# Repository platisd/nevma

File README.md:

# Nevma
A USB gadget to transform your gestures to keyboard and mouse events.

## Overview
Nevma (means "gesture" in Greek) is a simple to build, program and use device that translates your hand gestures into keyboard and mouse input. Just plug it in your USB port and magically wave through your presentations, documents, pictures, songs and the like.

## How does it work
Nevma implements two basic functions. Gesture recognition and keyboard and mouse event generation over USB. The former is realized through the [APDS-9960](https://learn.sparkfun.com/tutorials/apds-9960-rgb-and-gesture-sensor-hookup-guide) sensor while the latter by utilizing the USB HID capabilities of the ATMega32U4 chip.

Nevma can by default recognize a plethora of gestures; swipe left, right, up, down, and moving the hand closer or further from the sensor, using the [APDS-9960 library](https://github.com/sparkfun/SparkFun_APDS-9960_Sensor_Arduino_Library) by Sparkfun.

## Components
* [Nevma board PCB](https://www.pcbway.com/project/shareproject/Nevma__Gesture_control_for_the_masses.html)
* [3D printed case](https://www.tinkercad.com/things/h5ymCb1lX3J)
* [Mini SS Micro ATMEGA32U4](https://www.aliexpress.com/item/New-Arrival-Mini-SS-Micro-ATMEGA32U4-Pro-Micro-Module-Board-Compatible-For-Arduino/32777411276.html)
* [APDS-9960 module](https://www.aliexpress.com/item/GY-9960LLC-APDS-9960-RGB-and-Gesture-Sensor-Module-I2C-Breakout-for-Arduino/32746930049.html)

## Media
*  [Nevma: Gesture control for the masses](https://platis.solutions/blog/2017/11/27/nevma-gesture-control-for-the-masses/)

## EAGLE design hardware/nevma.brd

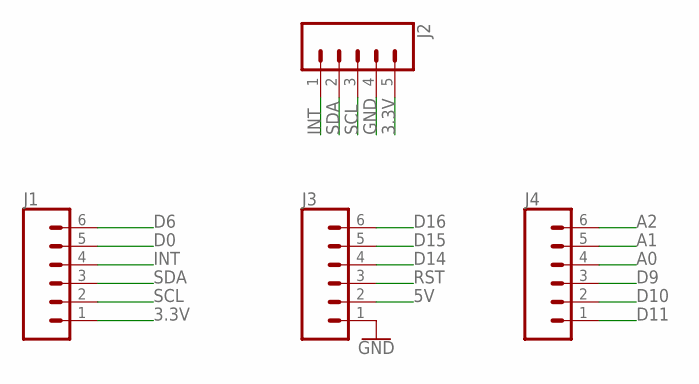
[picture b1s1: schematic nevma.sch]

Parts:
J1, J3, J4: CONN_06LOCK; 1X06_LOCK
J2: CONN_05LOCK; 1X05_LOCK

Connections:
3.3V: J1.1, J2.5
5V: J3.2
A0: J4.4
A1: J4.5
A2: J4.6
D0: J1.5
D6: J1.6
D9: J4.3
D10: J4.2
D11: J4.1
D14: J3.4
D15: J3.5
D16: J3.6
GND: J2.4, J3.1
INT: J1.4, J2.1
RST: J3.3
SCL: J1.2, J2.3
SDA: J1.3, J2.2

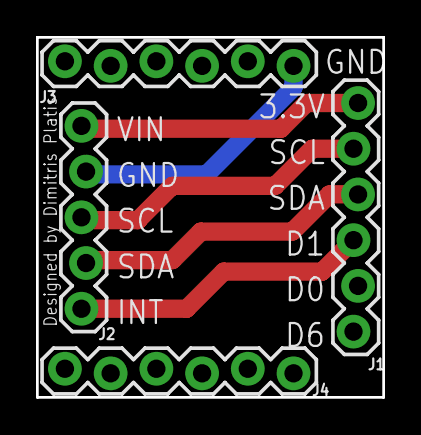
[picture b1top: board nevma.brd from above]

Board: 2 copper layers, 19.2 x 20.0 mm, 4 parts (0 on the bottom side), 5 nets.

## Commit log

2017-10-22 Add initial rev. 0 board
2017-10-22 Add licenses
2017-10-22 Correct resistor value
2017-10-22 Decrease board size
2017-10-27 Reduce board size This will allower the better fit of the USB socket
2017-11-01 New concept based on atmega32u4 board
    HW rev. 2
2017-11-01 Remove GPL license
    Since we are not using VUSB it is not necessary anymore
2017-11-08 Fix header position - HW rev. 2
    * Also slightly decrease board size
2017-11-08 Add nevma board firmware
2017-11-09 Decrease board size further
2017-11-09 Bugfix: Workaround for sensor hanging when gesturing too fast
2017-11-26 Add reversed controls and mouse scroll
2017-11-26 Add link to purchase PCB
2017-11-26 Add link to 3D printed case
2017-11-26 Add Nevma photo
2017-11-27 Fix link to article

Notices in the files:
parts and their libraries:
SparkFun-Connectors: Licensing: Creative Commons ShareAlike 4.0 International - https://creativecommons.org/licenses/by-sa/4.0
